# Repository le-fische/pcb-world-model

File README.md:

# PCB Engineering World Model (`rev1` $\to$ `rev15`)

**Closed-Loop Neuro-Symbolic Generative EDA, C++20 Octilinear Router, 8-Layer HDI, Multi-Zone Rigid-Flex $85\Omega$ PCIe Gen 4, Mixed-Signal $J_{\text{return}}$ & 3D PBR Workstation**

- **Live Interactive Multi-Revision Workstation (Vercel Production):** [https://pcb-world-model.vercel.app/](https://pcb-world-model.vercel.app/)
- **Live Interactive Multi-Revision Workstation (GitHub Pages):** [https://le-fische.github.io/pcb-world-model/](https://le-fische.github.io/pcb-world-model/)
- **Deep-Link Any Revision Directly:** [`#rev1`](https://le-fische.github.io/pcb-world-model/#rev1) · [`#rev2`](https://le-fische.github.io/pcb-world-model/#rev2) · [`#rev3`](https://le-fische.github.io/pcb-world-model/#rev3) · [`#rev4`](https://le-fische.github.io/pcb-world-model/#rev4) · [`#rev5`](https://le-fische.github.io/pcb-world-model/#rev5) · [`#rev6`](https://le-fische.github.io/pcb-world-model/#rev6) · [`#rev7`](https://le-fische.github.io/pcb-world-model/#rev7) · [`#rev8`](https://le-fische.github.io/pcb-world-model/#rev8) · [`#rev9`](https://le-fische.github.io/pcb-world-model/#rev9) · [`#rev10`](https://le-fische.github.io/pcb-world-model/#rev10) · [`#rev11`](https://le-fische.github.io/pcb-world-model/#rev11) · [`#rev12`](https://le-fische.github.io/pcb-world-model/#rev12) · [`#rev13`](https://le-fische.github.io/pcb-world-model/#rev13) · [`#rev14`](https://le-fische.github.io/pcb-world-model/#rev14) · [`#rev15`](https://le-fische.github.io/pcb-world-model/#rev15)

---

## Interactive Web Workstation Capabilities

The deployed workstation (`pcb-world-model/ui/web/`) includes pre-compiled geometry, traces, vias, 3D meshes, schematics, pinouts, and benchmark telemetry for every revision (`rev1` through `rev15`):

1. **Revision Ribbon & Deep-Linking (`REV 1` $\to$ `REV 15`):** Switch between any revision to inspect its exact routed boards, composite scores, via counts, and architectural unlocks.
2. **2D CAD Canvas:** 60 FPS pan/zoom, per-layer copper toggles (`F.Cu`, `B.Cu`, `In1`, `In2`), rigid-flex zone overlays, thermal isolation slots, and click-to-cross-probe net highlighting.
3. **Real-Time 3D PBR Viewport (Three.js):** Drilled FR4 substrate, 5 solder mask finishes (KiCad Green, Matte Black, Royal Blue, Crimson Red, Arctic White), ENIG immersion gold pads, procedural STEP-quality 3D components, and 180° board flip.
4. **Cross-Probed Schematic & Vector SVG Pin Diagrams:** Orthogonal functional-block schematic and package pinout inspector synced with 2D and 3D views.
5. **Tech Dossier, Benchmark Matrix, Side-by-Side Revision Diff & Rev 15 LLM Studio:** Read full `OVERVIEW.md` specs, compare any two revisions side-by-side, inspect frontier baselines, or test the `PromptPhysicsSpec` gatekeeper.
6. **1-Click `.kicad_pcb` Download:** Export the manufacturing-ready KiCad 8 S-expression file for any board in any revision directly from the browser.

---

## Revision Progression Matrix

| Revision | Status | Core Capability Unlocked | Target Boards | Composite Score | Overview Doc |
| :--- | :---: | :--- | :--- | :---: | :--- |
| **`rev1`** | **Verified & Frozen** | Closed-loop GATv2 Macro-Placer + Dual-Head U-Net World Model + Box-Dilated 45° Octilinear A* + DRC Rip-Up | `usb_uart_bridge`, `buck_converter`, `mcu_sensor_node` (2L) | **98.00 / 100** *(23/23 nets, 0 DRC, 27 vias, 6.88s)* | [`rev1/OVERVIEW.md`](pcb-world-model/revisions/rev1/OVERVIEW.md) |
| **`rev2`** | **Verified & Frozen** | Sub-Grid Euclidean Pad/Trace/Via Clearance Field + Full Steiner Copper Reuse + 2-Opt Component Swap | `usb_uart_bridge`, `buck_converter`, `mcu_sensor_node` (2L) | **99.26 / 100** *(23/23 nets, 0 DRC, 10 vias, 6.37s)* | [`rev2/OVERVIEW.md`](pcb-world-model/revisions/rev2/OVERVIEW.md) |
| **`rev3`** | **Verified & Frozen** | Per-Net Width Classes (`0.40mm` Power vs `0.25mm` Signal) + Blind Zero-Hint Placement (`--blind`) + `rp2040_minimal` | `B1–B3` + `B4: rp2040_minimal` (35 nets) | **99.28 / 100** *(98.33 `--blind`)* | [`rev3/OVERVIEW.md`](pcb-world-model/revisions/rev3/OVERVIEW.md) |
| **`rev4`** | **Verified & Frozen** | Parametric IPC-7351 Footprint Generator + Hierarchical Prompt-to-Netlist Composer & ERC + `B5: macropad_matrix` | Any prompt (`--prompt`) + `B1–B5` (44 nets) | **99.16 / 100** *(98.53 `--blind`)* | [`rev4/OVERVIEW.md`](pcb-world-model/revisions/rev4/OVERVIEW.md) |
| **`rev5`** | **Verified & Frozen** | Copper Ground Pour Zones + JLCPCB/PCBWay `bom.csv` & `positions.csv` Bundle + Barrel Reuse | Any prompt + `B1–B5` (44 nets) | **99.56 / 100** *(10 vias across 5 boards)* | [`rev5/OVERVIEW.md`](pcb-world-model/revisions/rev5/OVERVIEW.md) |
| **`rev6`** | **Verified & Frozen** | Native Compiled C++20 A* Kernel (`<0.5s`/board) + 4-Layer Internal Planes + SI/IPC-2221 Thermal Telemetry | `B1–B5` + `flight_controller_50` (50 comps, 4L) | **99.56 / 100** *(`1.73s` total; `43/43` FC in `3.88s`)* | [`rev6/OVERVIEW.md`](pcb-world-model/revisions/rev6/OVERVIEW.md) |
| **`rev7`** | **Verified & Frozen** | Interactive Pre-Flight Constraint Negotiator (`HTTP 409`) + Class A/B 12-Domain Library + Class C Ingest | `B1–B8` (`wearable_oled_keychain_26x26`) | **99.56 / 100** *(46/46 tests)* | [`rev7/OVERVIEW.md`](pcb-world-model/revisions/rev7/OVERVIEW.md) |
| **`rev8`** | **Verified & Frozen** | Verilog-2001 RTL Synthesis + `iverilog`/`Verilator` + Joint `.pcf` FPGA Pin-Swap (`iCE40UP5K`) + OpenLane `SKY130` | `B1–B5` + `B9: fpga_custom_protocol_bridge` (4L) | **99.56 / 100** *(`-92.5%` crossings `147->11`)* | [`rev8/OVERVIEW.md`](pcb-world-model/revisions/rev8/OVERVIEW.md) |
| **`rev9`** | **Verified & Frozen** | Real-Time PBR 3D Rendering + Procedural STEP 3D ICs + Interactive Vector SVG Pinouts + Cross-Probed Schematic | All Production Boards (`B1–B9`, `FC-50`) | **99.56 / 100** *(AP214 `.STEP` export)* | [`rev9/OVERVIEW.md`](pcb-world-model/revisions/rev9/OVERVIEW.md) |
| **`rev10`** | **Verified & Frozen** | 6-Rule DFM/DFA Craftsmanship Auditor + Automated Gerber/Excellon Drill CAM Bundler | All Production Boards (`B1–B9`, `FC-50`) | **99.29 / 100** *(100% DFM/DFA PASS; 59/59 tests)* | [`rev10/OVERVIEW.md`](pcb-world-model/revisions/rev10/OVERVIEW.md) |
| **`rev11`** | **Verified & Frozen** | Import `.kicad_sch`/Netlists + Datasheet Pinout Ingest + External `.STEP`/`.DXF` Enclosures + Lock-Preserving Re-Opt | `B10: step_enclosure_keychain`, `B11`, `B12` | **B10–B12 PASS** *(`-87.5%` vias on `B12`; 64/64 tests)* | [`rev11/OVERVIEW.md`](pcb-world-model/revisions/rev11/OVERVIEW.md) |
| **`rev12`** | **Verified & Frozen** | **8-Layer (`2+4+2`) HDI** + Buried Core Vias (`L3↔L6`) + Staggered-Only Microvia Lockout ($\Delta xy \ge 0.25\text{mm}$) | `B13: hdi_fpga_bga_fanout_8l` (64-ball `0.8mm` BGA) | **99.29 / 100** *(`0` stacked, `0` skip-vias; 68/68 tests)* | [`rev12/OVERVIEW.md`](pcb-world-model/revisions/rev12/OVERVIEW.md) |
| **`rev13`** | **Verified & Frozen** | Noisy (`5A 2MHz GaN`) vs. Quiet (`24-bit ADC`) Partitioning + Continuous `GND` + $J_{\text{return}}$ & Broadside Crosstalk | `B14: mixed_signal_gan_adc_30x50` + `B14a–c` | **99.29 / 100** *(`0.0%` $J_{\text{return}}$ overlap; 73/73 tests)* | [`rev13/OVERVIEW.md`](pcb-world-model/revisions/rev13/OVERVIEW.md) |
| **`rev14`** | **Active (Verified)** | Multi-Zone **`Rigid FR4` + `Cross-Hatched Flex`** + Coupled **$85\Omega$ PCIe Gen 4** + Skew Match + Under-BGA PDN | `B15: ultimate_rigid_flex_8l_hdi_pcie_gan_adc` | **99.29 / 100** *(`99.51` `--blind`; `78/78` tests)* | [`rev14/OVERVIEW.md`](pcb-world-model/revisions/rev14/OVERVIEW.md) |
| **`rev15`** | **Planned Spec** | Local **`qwen3-1.7b`** via **LM Studio** (`localhost:1234/v1` `strict: true` JSON Schema) $\to$ Gatekeeper | `B16: local_llm_physics_translator` | **Target: 100% Valid `PromptPhysicsSpec` JSON** | [`rev15/OVERVIEW.md`](pcb-world-model/revisions/rev15/OVERVIEW.md) |

---

## Local Quickstart

```bash
# 1. Run the full 78-test verification suite (rev1 -> rev14)
uv run pytest pcb-world-model/tests -v

# 2. Re-compile the static multi-revision dataset for Vercel / GitHub Pages
uv run python pcb-world-model/scripts/compile_revisions_dataset.py

# 3. Launch the live FastAPI + WebSocket server locally
uv run uvicorn ui.server:app --app-dir pcb-world-model --port 8050
```

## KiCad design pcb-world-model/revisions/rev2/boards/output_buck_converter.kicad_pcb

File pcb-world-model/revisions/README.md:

# `pcb-world-model` — Revision Control & Progressive Engineering Roadmap

This directory tracks every revision of the **PCB Engineering World Model**, from the initial closed-loop baseline (`rev1`) through DFM craftsmanship (`rev10`), external import optimization (`rev11`), the 3-stage high-speed rigid-flex HDI + adversarial electromagnetics capstone (`rev12` $\to$ `rev14`), and the lightweight local LLM physics-translator frontend (`rev15`).

---

## Revision Progression Matrix

| Revision | Status | Core Capability Unlocked | Target Boards | Composite Score | Overview & Setup Doc |
| :--- | :---: | :--- | :--- | :---: | :--- |
| **`rev1`** | **Verified & Frozen** | Closed-loop GATv2 Macro-Placer + Dual-Head U-Net World Model + Box-Dilated 45° Octilinear A* + DRC Rip-Up | `usb_uart_bridge`, `buck_converter`, `mcu_sensor_node` (2-Layer) | **98.00 / 100** *(23/23 nets, 0 DRC, 27 vias, 6.88s)* | [`rev1/OVERVIEW.md`](file:///Users/le/Documents/antigravity/kind-hypatia/pcb-world-model/revisions/rev1/OVERVIEW.md) |
| **`rev2`** | **Verified & Frozen** | Sub-Grid Euclidean Pad/Trace/Via Clearance Field + Full Steiner Copper Reuse + 2-Opt Component Swap & Pin Orientation Search | `usb_uart_bridge`, `buck_converter`, `mcu_sensor_node` (2-Layer) | **99.26 / 100** *(23/23 nets, 0 DRC, 10 vias, 1 iter, 6.37s)* | [`rev2/OVERVIEW.md`](file:///Users/le/Documents/antigravity/kind-hypatia/pcb-world-model/revisions/rev2/OVERVIEW.md) |
| **`rev3`** | **Verified & Frozen** | Per-Net Width Classes (`0.40mm` Power vs `0.25mm` Signal) + Blind Zero-Hint Placement (`--blind`) + High-Density `rp2040_minimal` (14 comps, 12 nets) | `B1–B3` + `B4: rp2040_minimal` (35 nets total) | **99.28 / 100** *(35/35 nets, 0 DRC, 13 vias; **98.33 / 100** in `--blind` mode)* | [`rev3/OVERVIEW.md`](file:///Users/le/Documents/antigravity/kind-hypatia/pcb-world-model/revisions/rev3/OVERVIEW.md) |
| **`rev4`** | **Verified & Frozen** | Parametric IPC-7351 Footprint Generator (`env/footprint_generator.py`) + Hierarchical Prompt-to-Netlist Composer & ERC (`models/composer/schematic_composer.py`) + `B5: macropad_matrix` | **Any natural-language prompt (`--prompt`)** + `B1–B5` (44 nets total) | **99.16 / 100** *(44/44 nets, 0 DRC, 19 vias; **98.53 / 100** in `--blind` mode)* | [`rev4/OVERVIEW.md`](file:///Users/le/Documents/antigravity/kind-hypatia/pcb-world-model/revisions/rev4/OVERVIEW.md) |
| **`rev5`** | **Verified** | Copper Ground Pour Zones + JLCPCB/PCBWay `bom.csv` & `positions.csv` Manufacturing Bundle + Live Prompt Web UI + Through-Hole Barrel Layer-Transition Reuse | **Any natural-language prompt** + `B1–B5` (44 nets total) | **99.56 / 100** *(44/44 nets, 0 DRC, **10 vias** across 5 boards; **99.02 / 100** in `--blind` mode; `31/31` tests)* | [`rev5/OVERVIEW.md`](file:///Users/le/Documents/antigravity/kind-hypatia/pcb-world-model/revisions/rev5/OVERVIEW.md) |
| **`rev6`** | **Verified** | Native Compiled C++20 A* Kernel (`<0.5s` per board) + 4-Layer Internal Power/GND Planes + SI/IPC-2221 Thermal Telemetry (`flight_controller_50`) | `B1–B5` + `flight_controller_50` (43 nets, 50 comps) | **99.56 / 100** *(44/44 nets, 0 DRC, `1.73s` total; `43/43` 4L FC in `3.88s`; `37/37` tests)* | [`rev6/OVERVIEW.md`](file:///Users/le/Documents/antigravity/kind-hypatia/pcb-world-model/revisions/rev6/OVERVIEW.md) |
| **`rev7`** | **Verified & Frozen** | Interactive Pre-Flight Constraint & Trade-Off Negotiator (`needs_input` / HTTP `409` rejection) + Two-Tier Class A/B 12-Domain Library + Class C (`.kicad_mod` / Datasheet Compiler) + 8 Special Layout Rules + 2L/4L/6L + REV 7 Web UI | `B1–B5` + `B6: wearable_oled_keychain_26x26`, `B7: non_tech_wearable_keychain`, `B8: impossible_box_negotiation` | **99.56 / 100** *(44/44 nets, 0 DRC, `1.77s`; `B6` `20/20`, `B7` `20/20`, `B8` `19/19` all **0 DRC**; `46/46` tests)* | [`rev7/OVERVIEW.md`](file:///Users/le/Documents/antigravity/kind-hypatia/pcb-world-model/revisions/rev7/OVERVIEW.md) |
| **`rev8`** | **Verified & Frozen** | Verilog-2001 RTL Synthesis + Real `iverilog`/`Verilator` Verification + Joint `.pcf` FPGA Pin-Swap PCB Co-Design (`iCE40UP5K`) + OpenLane `SKY130` `GDSII` + REV 8 Silicon Workbench UI | `B1–B5` + `B9: fpga_custom_protocol_bridge` (46 nets, 4L) | **99.56 / 100** *(44/44 nets, 0 DRC, `1.72s`; `B9`: `iverilog` `5/5` PASS, `-92.5%` crossings `147->11`, `46/46` **0 DRC**, `SI=PASS`, `4.29s`; `52/52` tests)* | [`rev8/OVERVIEW.md`](file:///Users/le/Documents/antigravity/kind-hypatia/pcb-world-model/revisions/rev8/OVERVIEW.md) |
| **`rev9`** | **Verified & Frozen** | Real-Time PBR Solder Mask/ENIG Gold/FR4 Rendering + Procedural STEP-Quality 3D Component Bodies + Interactive Vector SVG Pin Diagrams + Cross-Probed Schematic View + True `.STEP` Assembly Export (fixed AP214 colors & multi-solid chips) | All Boards (`B1–B9`, `FC-50`, Custom Prompts) | **99.56 / 100** *(44/44 nets, 0 DRC, `1.75s`; `0` browser console errors; `.STEP` AP214 export; `55/55` tests)* | [`rev9/OVERVIEW.md`](file:///Users/le/Documents/antigravity/kind-hypatia/pcb-world-model/revisions/rev9/OVERVIEW.md) |
| **`rev10`** | **Verified & Frozen** | Board Corner Fillets + Screw-Head MLCC Buffers + Pad/Via Teardrops + Symmetric Anti-Tombstone Pad Entry + Acid-Trap Removal + Preferred `0.32mm` Halos + Silkscreen Scrubbing + Test Points + `dfm_report.md` | All Production Boards (`B1–B9`, `FC-50`, Custom Prompts) | **99.29 / 100** *(44/44 nets, 0 DRC, `2.11s`; **99.38 / 100** `--blind`; **100% DFM/DFA Audit PASS**; **`59/59` tests**)* | [`rev10/OVERVIEW.md`](file:///Users/le/Documents/antigravity/kind-hypatia/pcb-world-model/revisions/rev10/OVERVIEW.md) |
| **`rev11`** | **Verified & Frozen** | Import `.kicad_sch`/Netlists (w/ Auto-ERC Advisor), Datasheet Pin Diagrams (`.png`/`.pdf`), External `.STEP`/`.DXF` Enclosures ($Z_{\max}$ Height Map + Port Windows + Bosses), and Partial `.kicad_pcb` Lock-Preserving Re-Optimization | `B10: step_enclosure_keychain`, `B11: datasheet_pinout_ingest`, `B12: legacy_kicad_reoptimize` | **B10–B12 PASS** *(`B10`: `20/20`, `0` 3D collisions; `B11`: `16/16`, `0` ERC/DRC; `B12`: `-87.5%` vias, `0` DRC/DFM; **`64/64` tests**)* | [`rev11/OVERVIEW.md`](file:///Users/le/Documents/antigravity/kind-hypatia/pcb-world-model/revisions/rev11/OVERVIEW.md) |
| **`rev12`** | **Verified & Frozen** | Expand to **8-Layer (`2+4+2`) HDI** + Buried Core Vias (`L3↔L6`) + Max 2 Lamination Cycle Enforcer + **Staggered-Only Microvia Reliability Lockout** ($\Delta xy \ge 0.25\text{mm}$) + `make_bga` FPGA BGA Fanout | `B13: hdi_fpga_bga_fanout_8l` (`30×50mm`, 64-ball `0.8mm` BGA) + `B1–B12` | **99.29 / 100** *(`B1–B5` 44/44, 0 DRC, `2.85s`; **`B13`**: `23/23`, `0` DRC, `95` uVias, `7` buried, **`0` stacked**, **`0` skip-vias**, `min_stagger=0.2828mm`, `3.12s`; **`68/68` tests**)* | [`rev12/OVERVIEW.md`](file:///Users/le/Documents/antigravity/kind-hypatia/pcb-world-model/revisions/rev12/OVERVIEW.md) |
| **`rev13`** | **Verified & Frozen** | Noisy (`5A 2MHz GaN`) vs. Quiet (`24-bit ADC`) Top-Layer Domain Partitioning + **Continuous `GND`** + $J_{\text{return}}$ Verifier + **Z-Axis Broadside Crosstalk**, **Star Ground Contradiction** & **Thermal-vs-Signal 80% Inpainting** | `B14: mixed_signal_gan_adc_30x50` + `B14a–c` Adversarial Traps + `B1–B13` | **99.29 / 100** *(`B1–B5` 44/44, 0 DRC, `2.23s` / `99.38` `--blind` in `2.18s`; **`B14`**: `15/15`, `0` DRC, `ContGND=True`, `Sep=28.07mm` (`22.01mm` `--blind`), `0.0%` $J_{\text{return}}$, `DFM=100.0`; **`B14a–c`**: all PASS (`0` broadside, `invalid_remote_star_ground` refused, thermal slot carved); **`73/73` tests**)* | [`rev13/OVERVIEW.md`](file:///Users/le/Documents/antigravity/kind-hypatia/pcb-world-model/revisions/rev13/OVERVIEW.md) |
| **`rev14`** | **Active in Repo (Verified)** | Multi-Zone **`Rigid FR4` + `Cross-Hatched Polyimide Flex`** + Coupled **$85\Omega$ PCIe Gen 4 Router** + Skew Matching ($\le 0.125\text{mm}$) + **PDN Mounting Inductance Test** (Rip-Up Remote Caps $\to$ Under-BGA Via-in-Pad) | `B15: ultimate_rigid_flex_8l_hdi_pcie_gan_adc` + `B15a: pdn_decoupling_inductance_trap` + `B1–B14c` | **99.29 / 100** *(`B1–B5` 44/44, 0 DRC, `2.25s` / **`99.51`** `--blind` in `2.19s`; **`B15`**: `19/19`, `0` DRC, `ContGND=True`, `Sep=22.66mm`, `0.0%` $J_{\text{return}}$, `0` stacked, `Z_rigid=86.72Ω`, `Z_flex=84.69Ω`, `skew=0.0mm`, `PDN=0.8974nH`, `DFM=97.84`, `1.49s`; **`B15a`**: `7.72->0.9225nH` Under-BGA, `6/6`, `0` DRC, `0.57s`; **`78/78` tests**)* | [`rev14/OVERVIEW.md`](file:///Users/le/Documents/antigravity/kind-hypatia/pcb-world-model/revisions/rev14/OVERVIEW.md) |
| **`rev15`** | **Planned Spec (Lightweight Local LLM Translator)** | Route Local **`qwen3-1.7b`** via **LM Studio** (`localhost:1234/v1` `strict: true` JSON Schema, or Ollama / Standalone App GGUF) into `constraint_negotiator.py` Gatekeeper (`--translator auto\|lmstudio\|ollama\|regex`) | `B16: local_llm_physics_translator` | **Target: 100% Valid `PromptPhysicsSpec` JSON, ~1.1–1.4 GB App Model (`qwen3-1.7b`), `0` Regressions** | [`rev15/OVERVIEW.md`](file:///Users/le/Documents/antigravity/kind-hypatia/pcb-world-model/revisions/rev15/OVERVIEW.md) |

---

## How to Run & Demo the Active `rev14` System

1. **Run the Full 78-Test Verification Suite (`rev1`–`rev14`, incl. Rigid-Flex 8L HDI, Cross-Hatched $85\Omega$ PCIe Gen 4, Skew Matching & Under-BGA PDN Migration):**
   ```bash
   uv run pytest pcb-world-model/tests -v
   ```
2. **Run the `rev14` `B15` & `B15a`, `rev13` `B14` & `B14a–c`, `rev12` `B13`, and `B1–B5` Benchmark Suites (Standard & Blind Modes):**
   ```bash
   uv run python pcb-world-model/scripts/05_run_benchmarks.py --rev14
   uv run python pcb-world-model/scripts/05_run_benchmarks.py --rev14 --blind
   uv run python pcb-world-model/scripts/05_run_benchmarks.py --rev13
   uv run python pcb-world-model/scripts/05_run_benchmarks.py --rev12
   uv run python pcb-world-model/scripts/05_run_benchmarks.py --revision "rev14"
   uv run python pcb-world-model/scripts/05_run_benchmarks.py --revision "rev14-blind" --blind
   ```
3. **Launch the Live 2D/3D PBR, Schematic, Mixed-Signal & Rigid-Flex Workstation (`REV 14`):**
   ```bash
   uv run uvicorn ui.server:app --app-dir pcb-world-model --port 8050
   ```

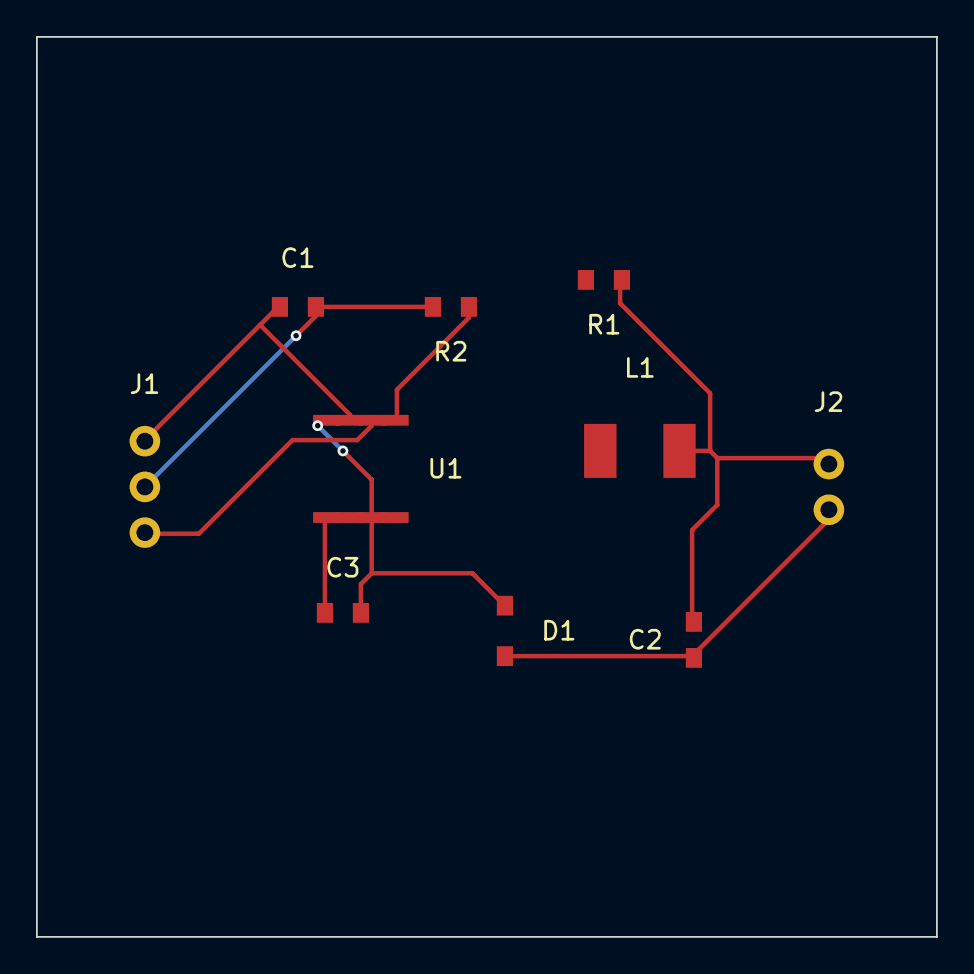
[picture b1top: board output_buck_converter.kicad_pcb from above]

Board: 2 copper layers, 50.0 x 50.0 mm, 10 parts (0 on the bottom side), 7 nets.

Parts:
C1: 22uF_IN; C_1206_3216Metric
C2: 47uF_OUT; C_1206_3216Metric
C3: 100nF_BST; C_0603_1608Metric
D1: SS34; D_SMA
J1: VIN_12V; TerminalBlock_bornier-3_P5.08mm
J2: VOUT_5V; TerminalBlock_bornier-2_P5.08mm
L1: 10uH; L_6.3x6.3_H3
R1: 100k; R_0603_1608Metric
R2: 18.7k; R_0603_1608Metric
U1: TPS54302; SOIC-8_3.9x4.9mm_P1.27mm

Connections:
BOOT: C3.1, U1.1
EN_CTRL: J1.3, U1.6
FB_DIV: R1.2, R2.1, U1.5
GND: C1.2, C2.2, D1.1, J1.2, J2.2, R2.2, U1.4
SW_NODE: C3.2, D1.2, L1.1, U1.3, U1.8
VIN_12V: C1.1, J1.1, U1.2, U1.7
VOUT_5V: C2.1, J2.1, L1.2, R1.1

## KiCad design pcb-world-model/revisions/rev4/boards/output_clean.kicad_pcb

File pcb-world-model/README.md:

# PCB Engineering World Model (`pcb-world-model` — Rev 1)

A closed-loop **Neuro-Symbolic PCB Engineering World Model** combining a **4-layer GATv2 Macro-Placement Composer**, a **Dual-Head Spatial World Model U-Net** (predicting future routing congestion $\hat{M}_{t+1}$ and scalar routability $V(S_t)$), a **45° Octilinear 2-Layer A* Router**, a **Deterministic 2D Geometric / Headless KiCad DRC Verifier**, and a live **FastAPI + WebSocket 2D/3D CAD Visualizer**.

## Architecture

1. **Data & Parser Layer (`env/`)**:
   - `sexpr_parser.py`: Recursive-descent `.kicad_pcb` S-expression parser translating footprints, pads, nets, segments, and vias into `NetlistGraph` (`Pad`, `ComponentNode`, `NetInfo`).
   - `board_state.py`: Maintains the `[C=7, H=250, W=250]` spatial state tensor $S_t$ (`board_outline`, `courtyard_mask`, `copper_L1`, `copper_L2`, `via_mask`, `active_net_pins`, `unrouted_demand`).
   - `kicad_exporter.py`: Exports manufacturing-ready KiCad 8 `.kicad_pcb` S-expressions.
2. **Macro-Placement Composer (`models/placer/`)**:
   - `gnn_encoder.py` & `placer_head.py`: 4-layer `GATv2Layer` encoder predicting continuous component poses $(x, y, \sin\theta, \cos\theta)$ with differentiable `SmoothHPWL`, courtyard `OverlapArea`, and `OutOfBounds` loss.
   - `relaxation.py`: 50-step gradient overlap repulsion, discrete 90° orientation optimization, and 0.5mm grid snapping.
3. **Latent Spatial World Model & Router (`models/world/`)**:
   - `dynamics_unet.py`: U-Net with bottleneck 2D spatial self-attention and dual heads for layer-wise congestion $\hat{M}_{t+1} \in [0, 1]^{2 \times H \times W}$ and scalar routability critic $V(S_t) \in [0, 1]$.
   - `neural_router.py`: 2-layer 45° octilinear MST-Steiner A* router guided by $\hat{M}_{t+1} + \text{Penalty}_{\text{DRC}}$.
4. **Deterministic Verifier (`verifier/`)**:
   - `fast_clearance.py` & `kicad_drc.py`: Millisecond 2D segment/pad/via/courtyard DRC engine plus headless `kicad-cli pcb drc --format json` integration with closed-loop rip-up & reroute penalty injection.
5. **Interactive Web Visualizer (`ui/`)**:
   - `server.py` & `web/`: FastAPI + WebSocket server streaming live $S_t \to S_{t+1}$ rollouts, 2D multi-layer CAD view, 3D isometric stackup view, all 7 spatial tensor channels, and `.kicad_pcb` inspection.

## Quickstart

```bash
# 1. Generate reference .kicad_pcb boards and synthetic World Model training triplets
uv run python pcb-world-model/scripts/01_generate_synthetic.py

# 2. Train GATv2 Macro-Placer
uv run python pcb-world-model/scripts/02_train_placer.py --epochs 25

# 3. Train Dual-Head Spatial World Model U-Net
uv run python pcb-world-model/scripts/03_train_world_model.py --epochs 20

# 4. Run closed-loop inference and export clean .kicad_pcb
uv run python pcb-world-model/scripts/04_run_inference.py --board mcu_sensor_node --output pcb-world-model/output_clean.kicad_pcb

# 5. Launch Interactive 2D/3D Web Console
uv run uvicorn ui.server:app --app-dir pcb-world-model --port 8050

# 6. Run Test Suite
uv run pytest pcb-world-model/tests -v
```

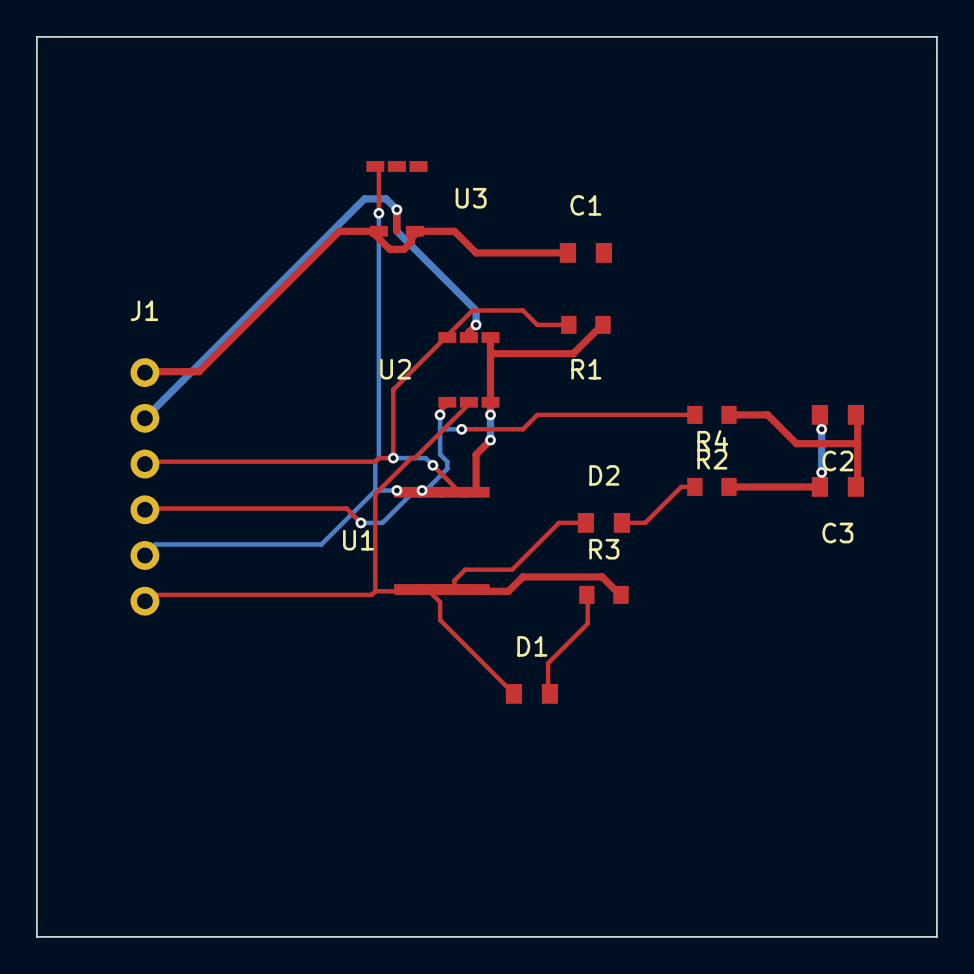
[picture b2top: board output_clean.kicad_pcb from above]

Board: 2 copper layers, 50.0 x 50.0 mm, 13 parts (0 on the bottom side), 11 nets.

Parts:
C1: 10uF_IN; C_0805_2012Metric
C2: 100nF_MCU; C_0805_2012Metric
C3: 100nF_SENS; C_0805_2012Metric
D1: STAT_LED1; LED_0805_2012Metric
D2: STAT_LED2; LED_0805_2012Metric
J1: HOST_HDR; PinHeader_1x06_P2.54mm_Vertical
R1: 4.7k_SDA; R_0603_1608Metric
R2: 4.7k_SCL; R_0603_1608Metric
R3: 1k_LED1; R_0603_1608Metric
R4: 1k_LED2; R_0603_1608Metric
U1: STM32G031; SOIC-8_3.9x4.9mm_P1.27mm
U2: BME280_I2C; SOT-23-6
U3: AP2112K-3.3; SOT-23-5

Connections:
GND: C1.2, C2.2, C3.2, J1.2, R3.2, R4.2, U1.8, U2.2, U3.2
I2C_SCL: J1.4, R2.2, U1.3, U2.4
I2C_SDA: J1.3, R1.2, U1.2, U2.3
LED1_K: D1.2, R3.1
LED2_K: D2.2, R4.1
MCU_RST: J1.5, U1.4, U3.5
SENSOR_INT: J1.6, U1.5, U2.5
STATUS_LED_1: D1.1, U1.6
STATUS_LED_2: D2.1, U1.7
VCC_3V3: C2.1, C3.1, R1.1, R2.1, U1.1, U2.1, U2.6, U3.4
VIN_5V: C1.1, J1.1, U3.1, U3.3

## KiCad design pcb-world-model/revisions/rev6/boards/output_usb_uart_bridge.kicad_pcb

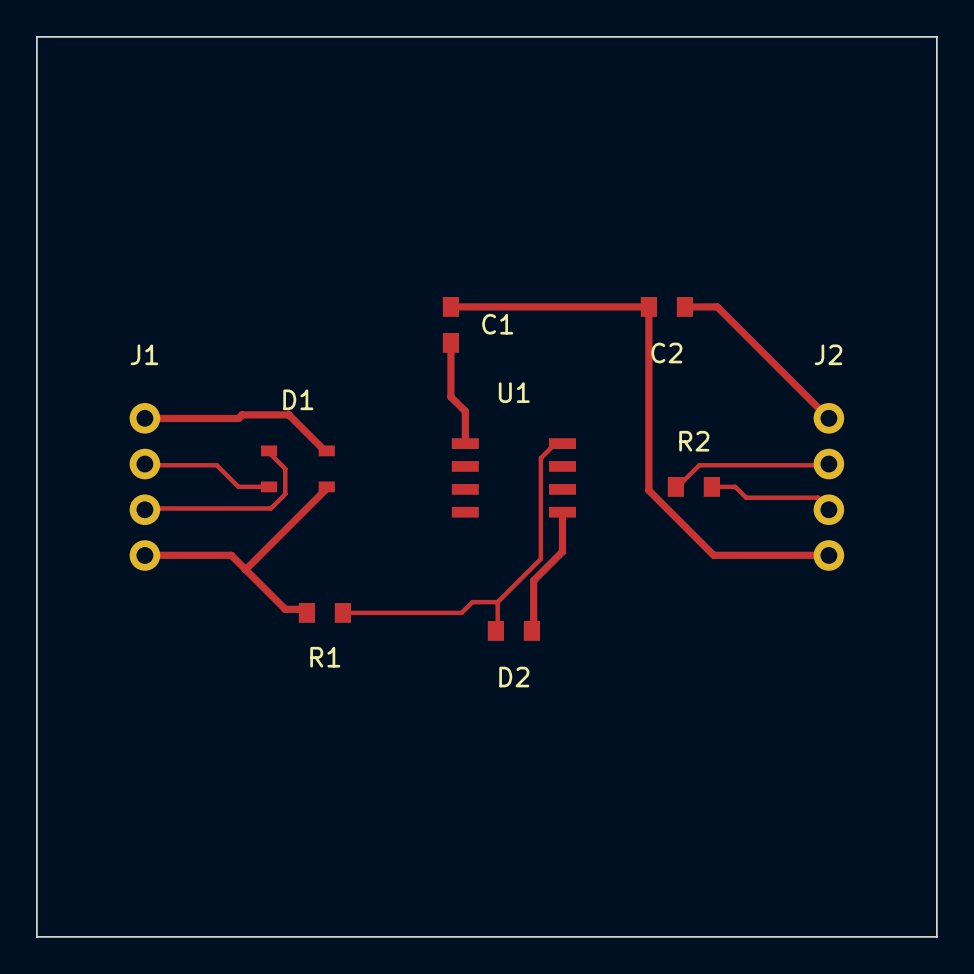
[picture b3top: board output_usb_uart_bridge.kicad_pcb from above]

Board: 2 copper layers, 50.0 x 50.0 mm, 9 parts (0 on the bottom side), 8 nets.

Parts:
C1: 10uF; C_0805_2012Metric
C2: 100nF; C_0805_2012Metric
D1: USBLC6-2SC6; SOT-23-6
D2: TX_LED; LED_0805_2012Metric
J1: USB_PORT; USB_Micro-B_Molex
J2: UART_HDR; PinHeader_1x04_P2.54mm_Vertical
R1: 470R; R_0603_1608Metric
R2: 0R_LOOP_OPT; R_0603_1608Metric
U1: CH340N_BRIDGE; SOIC-8_3.9x4.9mm_P1.27mm

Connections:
GND: C1.2, C2.2, D1.3, J1.4, J2.4, R1.2, U1.4
LED_ACT: D2.2, R1.1, U1.8
UART_RX: J2.3, R2.2, U1.7
UART_TX: J2.2, R2.1, U1.6
USB_DM: D1.2, J1.2, U1.3
USB_DP: D1.1, J1.3, U1.2
VBUS_5V: C1.1, D1.4, J1.1, U1.1
VCC_3V3: C2.1, D2.1, J2.1, U1.5

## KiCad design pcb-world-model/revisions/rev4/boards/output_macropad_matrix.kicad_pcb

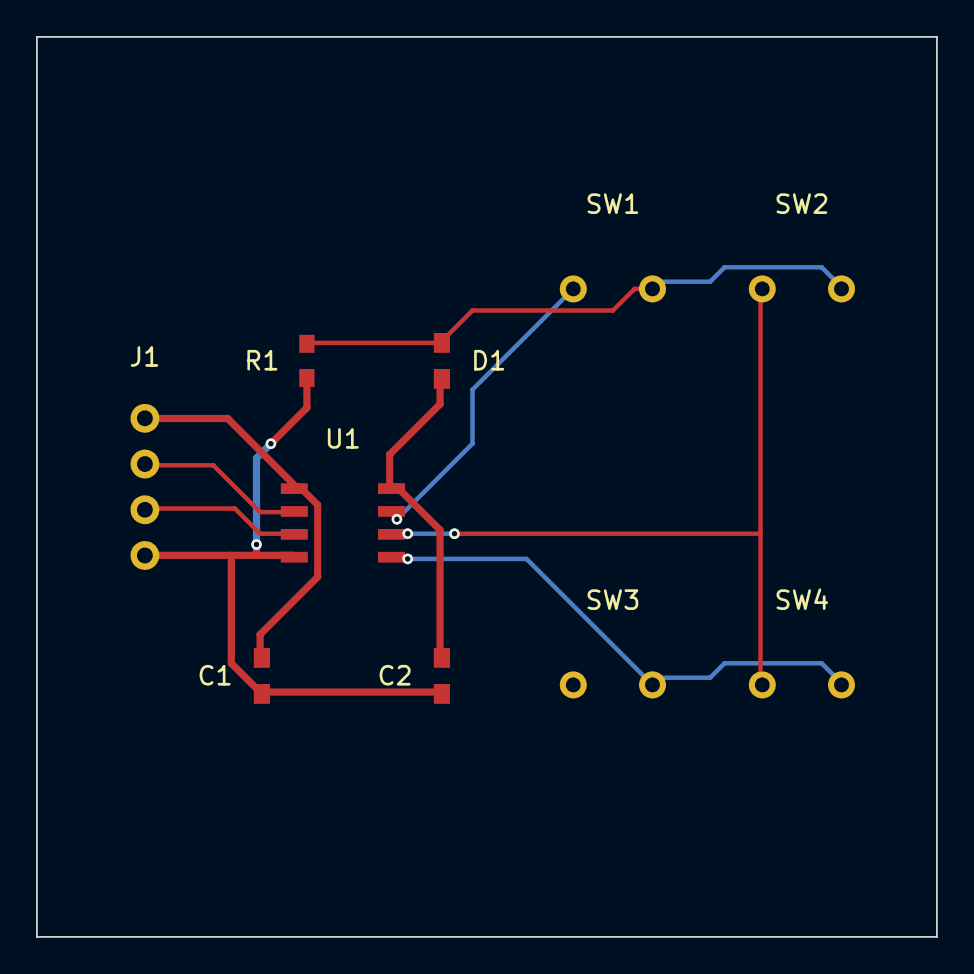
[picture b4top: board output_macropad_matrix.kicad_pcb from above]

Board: 2 copper layers, 50.0 x 50.0 mm, 10 parts (0 on the bottom side), 9 nets.

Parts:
C1: 10uF_VBUS; C_0805_2012Metric
C2: 100nF_VDD; C_0805_2012Metric
D1: ROW0_SCAN; LED_0805_2012Metric
J1: USB_HID_HDR; PinHeader_1x04_P2.54mm_Vertical
R1: 10k_ROW0; R_0603_1608Metric
SW1: KEY_1; SW_Cherry_MX_1.00u_PCB
SW2: KEY_2; SW_Cherry_MX_1.00u_PCB
SW3: KEY_3; SW_Cherry_MX_1.00u_PCB
SW4: KEY_4; SW_Cherry_MX_1.00u_PCB
U1: CH552G_HID; SOIC-8_3.9x4.9mm_P1.27mm

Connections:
COL0: SW1.1, SW3.1, U1.7
COL1: SW2.1, SW4.1, U1.6
GND: C1.2, C2.2, J1.4, R1.2, U1.4
ROW0: D1.2, R1.1, SW1.2, SW2.2
ROW1: SW3.2, SW4.2, U1.5
USB_DM: J1.2, U1.2
USB_DP: J1.3, U1.3
VBUS_5V: C1.1, J1.1, U1.1
VCC_3V3: C2.1, D1.1, U1.8

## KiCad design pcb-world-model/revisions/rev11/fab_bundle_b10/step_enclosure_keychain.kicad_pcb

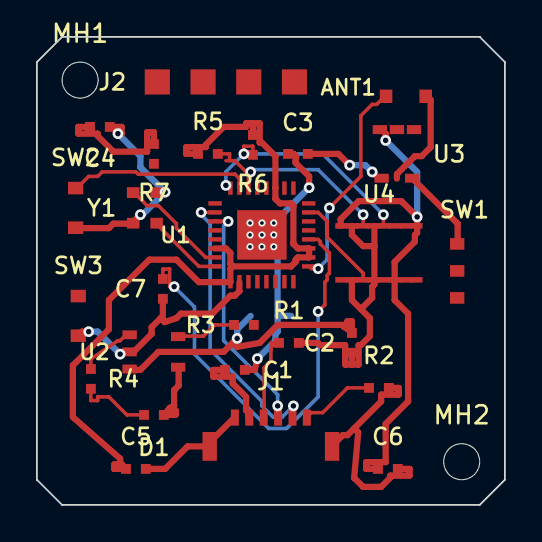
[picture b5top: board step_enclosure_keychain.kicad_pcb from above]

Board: 2 copper layers, 26.0 x 26.0 mm, 29 parts (1 on the bottom side), 20 nets.

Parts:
ANT1: ChipAntenna_2.4GHz; Johanson_2450AT18B100
C1: 4.7uF_VBUS; C_0402_1005Metric
C2: 4.7uF_VBAT; C_0402_1005Metric
C3: 1uF_LDO_IN; C_0402_1005Metric
C4: 1uF_LDO_OUT; C_0402_1005Metric
C5: 100nF_ESP; C_0402_1005Metric
C6: 100nF_LIS3DH; C_0402_1005Metric
C7: 100nF_EN; C_0402_1005Metric
D1: CHG_LED; LED_0402_1005Metric
J1: USB_C_6P; USB_C_Receptacle_6P
J2: SSD1306_OLED_4Pin; SolderPad_1x04_P2.54mm
J3: Rear_LiPo_SolderPads; SolderPad_1x02_P2.2mm_Back
MH1, MH2: MH_2.0mm; MountingHole_2.0mm_M2.0_NPTH
R1, R2: 5.1k; R_0402_1005Metric
R3: 10k_PROG_100mA; R_0402_1005Metric
R4: 1k_LED; R_0402_1005Metric
R5: 4.7k_SDA; R_0402_1005Metric
R6: 4.7k_SCL; R_0402_1005Metric
R7: 10k_EN; R_0402_1005Metric
SW1: SPDT_SlideSwitch_PCM12; SW_SPDT_PCM12
SW2, SW3: Tactile_Button_PTS810; SW_SPST_PTS810
U1: ESP32-C3FN4; QFN-32_5.0x5.0mm_P0.5mm
U2: MCP73831; SOT-23-5
U3: AP2112K-3.3; SOT-23-5
U4: LIS3DH; LGA-16_3.0x3.0mm_P0.6mm
Y1: XTAL_40MHz_2016; Crystal_SMD_2016-4Pin_2.0x1.6mm

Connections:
CHG_LED_A: D1.2, R4.1
CHG_PROG: R3.1, U2.5
CHG_STAT_K: R4.2, U2.1
CHIP_EN: C7.1, R7.2, SW3.1, U1.4
GND: ANT1.2, C1.2, C2.2, C3.2, C4.2, C5.2, C6.2, C7.2, J1.GND, J1.SH1, J1.SH2, J2.1, J3.2, R1.2, R2.2, R3.2, SW1.3, SW2.2, SW3.2, U1.26, U1.33, U2.2, U3.2, U4.5, U4.7, U4.10, U4.12, Y1.2, Y1.4
GPIO9_BOOT: SW2.1, U1.15
I2C_SCL: J2.3, R6.2, U1.16, U4.4
I2C_SDA: J2.4, R5.2, U1.14, U4.6
IMU_INT1: U1.7, U4.11
RF_ANT: ANT1.1, U1.1
USB_CC1: J1.CC1, R1.1
USB_CC2: J1.CC2, R2.1
USB_DM: J1.D-, U1.18
USB_DP: J1.D+, U1.19
VBAT: C2.1, J3.1, SW1.2, U2.3
VBAT_SW: C3.1, SW1.1, U3.1, U3.3
VBUS_5V: C1.1, D1.1, J1.VBUS, U2.4
VCC_3V3: C4.1, C5.1, C6.1, J2.2, R5.1, R6.1, R7.1, U1.2, U1.3, U1.11, U1.17, U1.22, U1.25, U3.5, U4.1, U4.8, U4.14
XTAL_N: U1.24, Y1.3
XTAL_P: U1.23, Y1.1

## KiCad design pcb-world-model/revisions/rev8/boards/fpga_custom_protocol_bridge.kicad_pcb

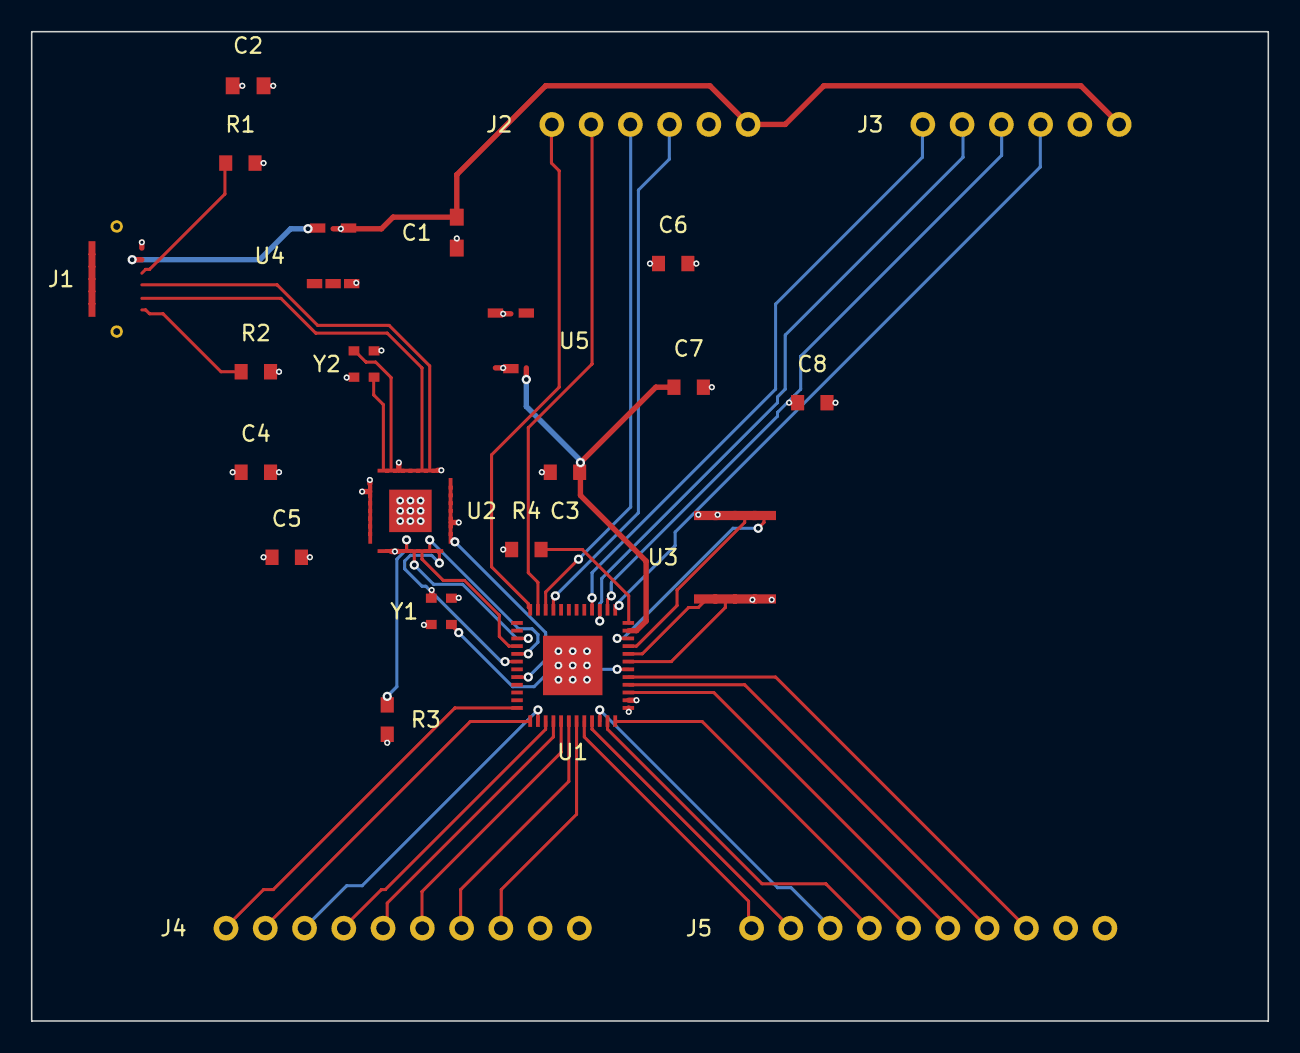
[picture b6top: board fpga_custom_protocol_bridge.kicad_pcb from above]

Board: 4 copper layers, 80.0 x 64.0 mm, 24 parts (0 on the bottom side), 46 nets.

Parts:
C1: 10uF_5V; C_0805_2012Metric
C2: 10uF_3V3; C_0805_2012Metric
C3: 1uF_1V2; C_0603_1608Metric
C4: 100nF_ESP1; C_0603_1608Metric
C5: 100nF_ESP2; C_0603_1608Metric
C6: 100nF_FPGA_IO; C_0603_1608Metric
C7: 100nF_FPGA_CORE; C_0603_1608Metric
C8: 100nF_FLASH; C_0603_1608Metric
J1: USB_C_6P; USB_C_Receptacle_6P
J2: WS2812_CH0_3; PinHeader_1x06_P2.54mm
J3: WS2812_CH4_7; PinHeader_1x06_P2.54mm
J4: ENC_CH0_3; PinHeader_1x10_P2.54mm
J5: ENC_CH4_7; PinHeader_1x10_P2.54mm
R1: 5.1k_CC1; R_0603_1608Metric
R2: 5.1k_CC2; R_0603_1608Metric
R3: 10k_ESP_EN; R_0603_1608Metric
R4: 10k_CRESET; R_0603_1608Metric
U1: Lattice_iCE40UP5K; QFN-48_7.0x7.0mm_P0.5mm
U2: ESP32-C3FN4; QFN-32_5.0x5.0mm_P0.5mm
U3: W25Q16; SOIC-8_3.9x4.9mm_P1.27mm
U4: AP2112K-3.3; SOT-23-5
U5: XC6206; SOT-23-3
Y1, Y2: XTAL_40MHz_2016; Crystal_SMD_2016-4Pin_2.0x1.6mm

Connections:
ENC0_A: J4.3, U1.43
ENC0_B: J4.4, U1.42
ENC1_A: J4.5, U1.41
ENC1_B: J4.6, U1.40
ENC2_A: J4.7, U1.39
ENC2_B: J4.8, U1.38
ENC3_A: J4.9, U1.37
ENC3_B: J4.10, U1.36
ENC4_A: J5.3, U1.5
ENC4_B: J5.4, U1.4
ENC5_A: J5.5, U1.3
ENC5_B: J5.6, U1.48
ENC6_A: J5.7, U1.47
ENC6_B: J5.8, U1.46
ENC7_A: J5.9, U1.45
ENC7_B: J5.10, U1.44
ESP_EN: R3.2, U2.4
ESP_SPI_CS_N: U1.30, U2.8
ESP_SPI_MISO: U1.29, U2.7
ESP_SPI_MOSI: U1.28, U2.6
ESP_SPI_SCK: U1.27, U2.5
ESP_XTAL_N: U2.24, Y2.3
ESP_XTAL_P: U2.23, Y2.1
FLASH_CS_N: U1.10, U3.1
FLASH_MISO: U1.9, U3.2
FLASH_MOSI: U1.8, U3.5
FLASH_SCK: U1.7, U3.6
FPGA_CLK_48M: U1.6, Y1.3
FPGA_CRESET_N: R4.2, U1.12
FPGA_IRQ_N: U1.32, U2.9
GND: C1.2, C2.2, C3.2, C4.2, C5.2, C6.2, C7.2, C8.2, J1.GND, J1.SH1, J1.SH2, J2.2, J3.2, J4.2, J5.2, R1.2, R2.2, U1.2, U1.49, U2.26, U2.33, U3.4, U4.2, U5.1, Y1.2, Y1.4, Y2.2, Y2.4
USB_CC1: J1.CC1, R1.1
USB_CC2: J1.CC2, R2.1
USB_DM: J1.D-, U2.19
USB_DP: J1.D+, U2.18
VBUS_5V: C1.1, J1.VBUS, J2.1, J3.1, U4.1, U4.3
VCC_1V2: C3.1, C7.1, U1.11, U5.2
VCC_3V3: C2.1, C4.1, C5.1, C6.1, C8.1, J4.1, J5.1, R3.1, R4.1, U1.1, U2.2, U2.3, U2.11, U2.17, U2.22, U2.25, U3.3, U3.7, U3.8, U4.5, U5.3, Y1.1
WS_CH0: J2.3, U1.21
WS_CH1: J2.4, U1.22
WS_CH2: J2.5, U1.23
WS_CH3: J2.6, U1.24
WS_CH4: J3.3, U1.13
WS_CH5: J3.4, U1.14
WS_CH6: J3.5, U1.15
WS_CH7: J3.6, U1.16

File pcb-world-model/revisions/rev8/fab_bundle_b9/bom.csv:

Comment,Designator,Footprint,Quantity
10uF_5V,C1,Capacitor_SMD:C_0805_2012Metric,1
10uF_3V3,C2,Capacitor_SMD:C_0805_2012Metric,1
1uF_1V2,C3,Capacitor_SMD:C_0603_1608Metric,1
100nF_ESP1,C4,Capacitor_SMD:C_0603_1608Metric,1
100nF_ESP2,C5,Capacitor_SMD:C_0603_1608Metric,1
100nF_FPGA_IO,C6,Capacitor_SMD:C_0603_1608Metric,1
100nF_FPGA_CORE,C7,Capacitor_SMD:C_0603_1608Metric,1
100nF_FLASH,C8,Capacitor_SMD:C_0603_1608Metric,1
USB_C_6P,J1,Connector_USB:USB_C_Receptacle_6P,1
WS2812_CH0_3,J2,Connector_PinHeader_2.54mm:PinHeader_1x06_P2.54mm,1
WS2812_CH4_7,J3,Connector_PinHeader_2.54mm:PinHeader_1x06_P2.54mm,1
ENC_CH0_3,J4,Connector_PinHeader_2.54mm:PinHeader_1x10_P2.54mm,1
ENC_CH4_7,J5,Connector_PinHeader_2.54mm:PinHeader_1x10_P2.54mm,1
5.1k_CC1,R1,Resistor_SMD:R_0603_1608Metric,1
5.1k_CC2,R2,Resistor_SMD:R_0603_1608Metric,1
10k_ESP_EN,R3,Resistor_SMD:R_0603_1608Metric,1
10k_CRESET,R4,Resistor_SMD:R_0603_1608Metric,1
Lattice_iCE40UP5K,U1,Package_DFN_QFN:QFN-48_7.0x7.0mm_P0.5mm,1
ESP32-C3FN4,U2,Package_DFN_QFN:QFN-32_5.0x5.0mm_P0.5mm,1
W25Q16,U3,Package_SO:SOIC-8_3.9x4.9mm_P1.27mm,1
AP2112K-3.3,U4,Package_TO_SOT_SMD:SOT-23-5,1
XC6206,U5,Package_TO_SOT_SMD:SOT-23-3,1
XTAL_40MHz_2016,"Y1,Y2",Crystal:Crystal_SMD_2016-4Pin_2.0x1.6mm,2

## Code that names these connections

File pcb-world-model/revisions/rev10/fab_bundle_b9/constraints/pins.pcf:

# Physical Constraints File (.pcf) for quad_ws2812_spi on Lattice_iCE40UP5K
# Generated by PCB Engineering World Model (rev8 Joint Silicon-PCB Co-Design)

set_io enc5_a             3     # net=ENC5_A
set_io enc4_b             4     # net=ENC4_B
set_io enc4_a             5     # net=ENC4_A
set_io fpga_clk_48m       6     # net=FPGA_CLK_48M
set_io flash_sck          7     # net=FLASH_SCK
set_io flash_mosi         8     # net=FLASH_MOSI
set_io flash_miso         9     # net=FLASH_MISO
set_io flash_cs_n         10    # net=FLASH_CS_N
set_io fpga_creset_n      12    # net=FPGA_CRESET_N
set_io ws_ch4             13    # net=WS_CH4
set_io ws_ch5             14    # net=WS_CH5
set_io ws_ch6             15    # net=WS_CH6
set_io ws_ch7             16    # net=WS_CH7
set_io ws_ch0             21    # net=WS_CH0
set_io ws_ch1             22    # net=WS_CH1
set_io ws_ch2             23    # net=WS_CH2
set_io ws_ch3             24    # net=WS_CH3
set_io esp_spi_sck        27    # net=ESP_SPI_SCK
set_io esp_spi_mosi       28    # net=ESP_SPI_MOSI
set_io esp_spi_miso       29    # net=ESP_SPI_MISO
set_io esp_spi_cs_n       30    # net=ESP_SPI_CS_N
set_io fpga_irq_n         32    # net=FPGA_IRQ_N
set_io enc3_b             36    # net=ENC3_B
set_io enc3_a             37    # net=ENC3_A
set_io enc2_b             38    # net=ENC2_B
set_io enc2_a             39    # net=ENC2_A
set_io enc1_b             40    # net=ENC1_B
set_io enc1_a             41    # net=ENC1_A
set_io enc0_b             42    # net=ENC0_B
set_io enc0_a             43    # net=ENC0_A
set_io enc7_b             44    # net=ENC7_B
set_io enc7_a             45    # net=ENC7_A
set_io enc6_b             46    # net=ENC6_B
set_io enc6_a             47    # net=ENC6_A
set_io enc5_b             48    # net=ENC5_B
